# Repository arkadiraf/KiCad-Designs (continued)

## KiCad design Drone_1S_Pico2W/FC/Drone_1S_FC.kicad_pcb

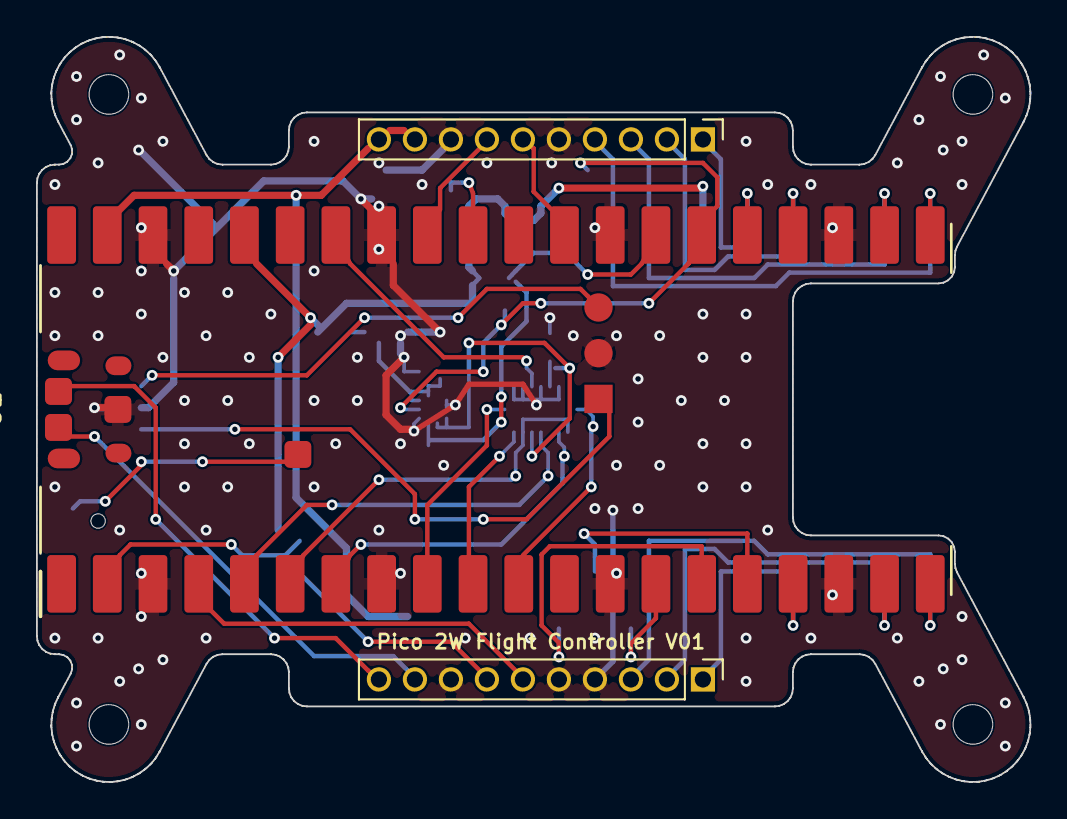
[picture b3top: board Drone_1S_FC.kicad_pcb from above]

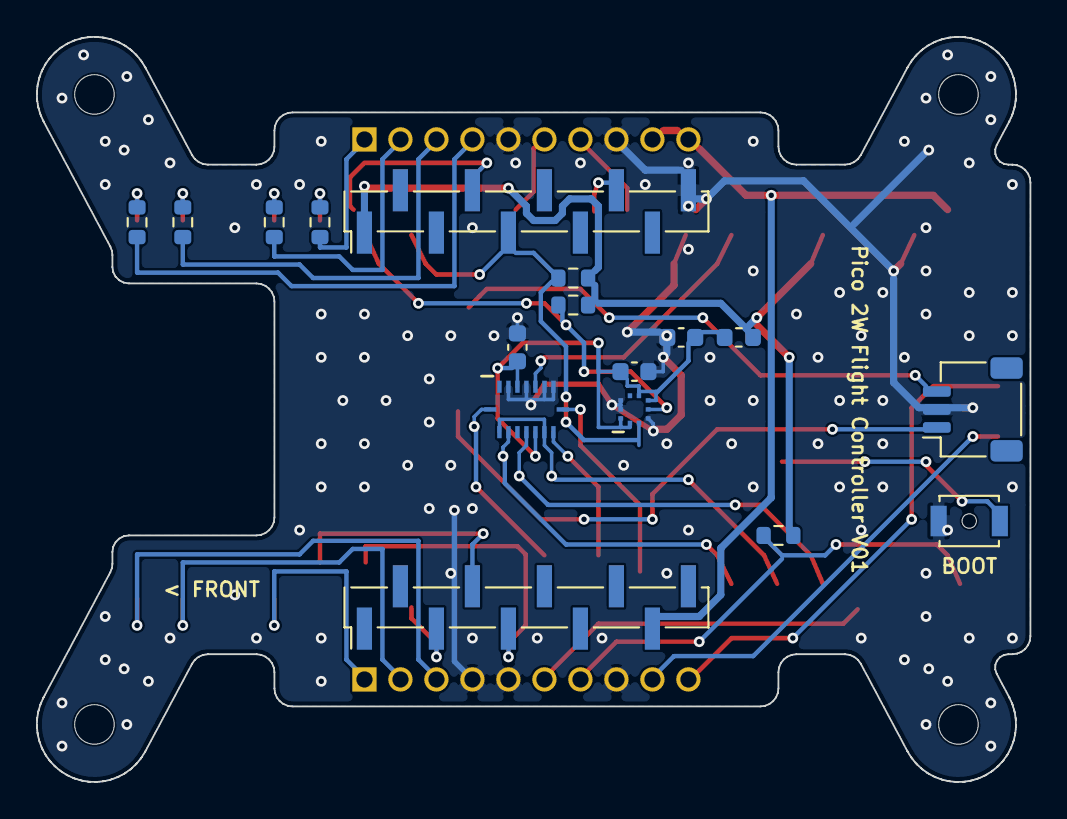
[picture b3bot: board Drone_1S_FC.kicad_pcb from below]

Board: 2 copper layers, 55.2 x 41.4 mm, 24 parts (17 on the bottom side), 37 nets.

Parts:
C1, C2: 100n; C_0603_1608Metric
C3: 4.7u; C_0603_1608Metric
H1, H2, H3, H4: M2x20 bolt + 7 mm spacer to frame; MountingHole_2.2mm_M2
J1, J2: Wurth 62001011121 header 1x10 2.00mm male (to fra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; PinHeader_1x10_P2.00mm_Vertical
J9: SWD (DNP): SWCLK, GND, SWDIO; JST_SH_SM03B-SRSS-TB_1x03-1MP_P1.00mm_Horizontal
L1: 1uH; L_0603_1608Metric
P1: Flow deck left (P1), male 1x10 2.00mm SMD; PinHeader_1x10_P2.00mm_Vertical_SMD_Pin1Left
P2: Flow deck right (P2), male 1x10 2.00mm SMD; PinHeader_1x10_P2.00mm_Vertical_SMD_Pin1Left
R1, R2: 4.7k; R_0603_1608Metric
R3, R4, R5, R6: 100; R_0603_1608Metric
R7: 47k; R_0603_1608Metric
SW1: BOOTSEL B3U-1000PM-B (Pico TP6 to GND); SW_SPST_B3U-1000P-B
U1: RPi_Pico_2_W; RPi_Pico_2_W_SMD_Castellated
U2: BMI088; Bosch_LGA-16_3x4.5mm_P0.5mm
U3: BMP390; Bosch_LGA-10_2x2mm_P0.5mm

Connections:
3V3: L1.1, P1.1, R1.1, R2.1, R7.1, U1.36
3V3_SENS: C1.1, C2.1, C3.1, L1.2, U2.3, U2.11, U3.1, U3.5, U3.6, U3.10
BOOST_EN: J1.6, U1.29
BOOTSEL: SW1.1, U1.TP6
CHG_PG: J1.7, U1.32
DSHOT1: J1.1, R3.2
DSHOT1_MCU: R3.1, U1.25
DSHOT2: J1.2, R4.2
DSHOT2_MCU: R4.1, U1.24
DSHOT3: J1.3, R5.2
DSHOT3_MCU: R5.1, U1.22
DSHOT4: J1.4, R6.2
DSHOT4_MCU: R6.1, U1.21
FLOW_CS: P1.8, U1.31
GND: C1.2, C2.2, C3.2, J1.5, J1.8, J2.4, J2.5, J2.8, J9.2, P1.10, SW1.2, U1.3, U1.8, U1.13, U1.18, U1.23, U1.28, U1.33, U1.38, U1.SWD_GND, U1.TP1, U2.2, U2.4, U2.6, U2.7, U3.3, U3.8, U3.9
I2C_SCL: P1.5, R2.2, U1.27, U3.2
I2C_SDA: P1.4, R1.2, U1.26, U3.4
IMU_CS_ACC: U1.7, U2.14
IMU_CS_GYR: U1.34, U2.5
IMU_INT_ACC: U1.11, U2.16
IMU_INT_GYR: U1.5, U2.12
MOTOR_PG: J2.7, R7.2, U1.2
ON1: J2.1, U1.17
ON2: J2.2, U1.19
ON3: J2.3, U1.20
ON4: J2.6, U1.4
SPI0_MISO: U1.6, U2.10, U2.15
SPI0_MOSI: U1.10, U2.9
SPI0_SCK: U1.9, U2.8
SPI1_MISO: P2.4, U1.16
SPI1_MOSI: P2.5, U1.15
SPI1_SCK: P2.3, U1.14
SWCLK: J9.1, U1.SWCLK
SWDIO: J9.3, U1.SWDIO
USB_DM: J2.10, U1.TP2
USB_DP: J2.9, U1.TP3
VSYS: J1.9, J1.10, P2.9, U1.39

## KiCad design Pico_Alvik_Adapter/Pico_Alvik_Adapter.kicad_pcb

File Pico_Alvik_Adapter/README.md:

# Pico Alvik Adapter

Adapter board that lets a **Raspberry Pi Pico W** replace the **Arduino Nano ESP32**
as the main controller of the **Arduino Alvik** robot (AKX00066).

* The Pico W is soldered **flat on the top side by its castellated edge pads**,
  with no pin headers between the boards.
* The bottom side carries two **1x15 2.54 mm SMD male headers in the Arduino Nano
  footprint**. They plug into the Alvik's Nano socket in place of the Nano ESP32.
* Every Nano pin the Alvik uses (UART, BOOT0, NRST, NANO_CHK, ROBOT_CHK, I2C,
  VIN, 3V3, GND) goes to a matching Pico pin: UART1 for the STM32 link and I2C1
  for the I2C bus. Seven spare Nano pins are wired as well.
* The micro-USB connector of the Pico sits at the same end as the Nano's USB-C,
  so it stays reachable through the Alvik's rear opening.

Designed in KiCad (files saved in KiCad 7 format; they open in KiCad 7, 8 and 9).

Individual renders are in `fabrication/docs/render_*.png`.

| | |
|---|---|
| Board size | 24.0 x 51.0 mm, 2 layers, 1.6 mm FR4 |
| Pico W | 21 x 51 mm module, top side, castellated SMD |
| Nano headers | 2x TE Connectivity 6-146132-3 (1x15 2.54 mm SMD male), bottom side, rows 15.24 mm apart |
| Antenna | 14 x 9 mm board notch under the Pico W antenna (datasheet keep-out) |

## Project layout

```
Pico_Alvik_Adapter.kicad_pro / .kicad_sch / .kicad_pcb   KiCad project
PicoAlvik.kicad_sym, PicoAlvik.pretty/                   project-local symbols & footprints
sym-lib-table, fp-lib-table                              library tables (use ${KIPRJMOD})
tools/                                                   generator scripts (design.py is the single source of truth)
firmware/                                                Alvik MicroPython library port kit for the Pico W
fabrication/                                             OSH Park gerbers (RS-274X) + drill, top/bottom stencils, BOM, positions, PDFs, renders
Materials/                                               datasheets / pinouts / schematics used for the design
```

## Pin mapping

Nano header pin numbers use the classic Nano numbering (1 = D1/TX ... 30 = VIN).

**Pins used by the Alvik** (from Arduino's `arduino-alvik-mpy` library, `pinout_definitions.py` and `uart.py`, plus the
Alvik datasheet block diagram; copies in `Materials/extracted/`):

| Nano pin | J1 | Pico GPIO | U1 pin | Alvik function | Pico peripheral |
|---|---|---|---|---|---|
| D1/TX1 | 1 | GP20 | 26 | UART TX -> STM32 RX (460800 baud) | UART1 TX |
| D0/RX0 | 2 | GP21 | 27 | UART RX <- STM32 TX | UART1 RX |
| D2 | 5 | GP22 | 29 | STM32 BOOT0 | |
| D3 | 6 | GP26 | 31 | STM32 NRST | |
| D4 | 7 | GP27 | 32 | NANO_CHK (EXT_CHK) | |
| A4/SDA | 23 | GP6 | 9 | I2C SDA (Qwiic / Grove, BMS, IMU...) | I2C1 SDA |
| A5/SCL | 24 | GP7 | 10 | I2C SCL | I2C1 SCL |
| A6 | 25 | GP8 | 11 | ROBOT_CHK (input) | |
| 3V3 | 17 | 3V3(OUT) | 36 | +3V3_EXT supply of the Alvik | via JP2 (bridged) |
| VBUS/VUSB | 27 | VBUS | 40 | Alvik power / charge input (USB 5V) | direct |
| VIN | 30 | VSYS | 39 | Alvik power output to the controller | D1 Schottky (opt. 0 Ω) |
| GND | 4, 29 | GND | 3,8,13,18,23,28,33,38 | | |
| RST | 3 | RUN | 30 | (not used by the Alvik) | via JP3 (open) |

**Spare Nano pins** (the Alvik leaves these unconnected). The ones that route cleanly are wired anyway:

| Nano pin | J1 | Pico GPIO | U1 pin | Note |
|---|---|---|---|---|
| D5 | 8 | GP28 | 34 | ADC2 |
| D13 | 16 | GP1 | 2 | |
| A0 | 19 | GP2 | 4 | |
| A1 | 20 | GP3 | 5 | |
| A2 | 21 | GP4 | 6 | |
| A3 | 22 | GP5 | 7 | |
| A7 | 26 | GP9 | 12 | |

Not connected: Nano D6–D12, B0, B1. Pico GP0, GP10–GP19,
ADC_VREF and 3V3_EN.

Each group is assigned in the same order on both sides, so its tracks never cross. The Nano-side
order is kept on the Pico's right edge (TX/RX/D2–D4) and left edge (A4–A6).

## Power design

How the Alvik uses the controller's power pins:

* **VBUS/VUSB (Nano pin 27):** the Alvik's power / battery-charge **input**. On a Nano this pin is raw
  USB 5V; the Nano schematic shows the USB-C VBUS pins tied straight to the `VUSB` header pin.
* **VIN (Nano pin 30):** the Alvik's power **output** to the controller. On a Nano, VIN is the input of
  its MP2322 regulator.

The adapter:

| Situation | Path |
|---|---|
| USB plugged into the Pico | Pico VBUS -> **Nano VUSB pin, direct** -> Alvik (powers the robot / charges the 18650) |
| | Pico VBUS -> Pico on-board Schottky -> VSYS (powers the Pico) |
| USB unplugged | Alvik VIN output -> **D1** -> VSYS (Alvik powers the Pico) |
| Both present | VSYS is diode-OR'ed (D1 / Pico diode); the higher source supplies the Pico |

* **D1: Nexperia PMEG6020ER,115** (2 A / 60 V Schottky, SOD-123W, anode = VIN; Digi-Key 1727-5217-1-ND;
  datasheet in `Materials/`, KiCad pads match its reflow land pattern 1.2 x 1.2 mm at 2.8 mm pitch). It stops the USB-derived
  VSYS (about 4.7 V) from back-feeding the Alvik's VIN output, in case the Alvik has no diode of its own
  there. Blocking that direction costs nothing, because the Alvik takes its power from VUSB, not VIN.
* **Option: 1206 0 Ω on the D1 pads.** This removes the ~0.35 V drop and matches a Nano exactly, where
  VIN is the regulator input with no diode and USB reaches VIN through the Nano's own PMEG6020. Only fit
  it if you know the Alvik's VIN output tolerates that.
* Charge current flows from the Pico's micro-USB straight to the VUSB pin. It does not pass through the
  Pico's 1 A on-board diode, or through D1.
* **VSYS range is 1.8–5.5 V.** The Alvik VIN output minus the D1 drop is inside that range.
* **JP2 (bridged):** Pico 3V3(OUT) -> Nano 3V3 pin. On the Nano, 3V3 is the output of its regulator,
  and on the Alvik it feeds `+3V3_EXT` (the I2C switch supply). Keep the 3V3 load under 300 mA. If you
  ever measure about 3.3 V on the Alvik's 3V3 socket pin with no controller fitted, cut JP2.
* **JP3 (open):** optional, Nano RST -> Pico RUN.
* C1: 10 µF on VSYS.

**Bring-up check:** with the adapter removed and the Alvik switched on, measure the Alvik's Nano socket.
VIN (pin 30) should be ≤ 5.5 V. VUSB (pin 27) and 3V3 (pin 17) should be about 0 V.

## Manufacturing

`fabrication/README.md` covers ordering and assembly. In short:

* **PCB:** `fabrication/Pico_Alvik_Adapter_OSHPark.zip`, RS-274X Gerbers with Protel names
  (`.GTL/.GBL/.GTS/.GBS/.GTO/.GBO/.GKO`) plus Excellon `.XLN`. Designed to OSH Park's rules: copper
  ≥ 0.4 mm from the board edge, drills ≥ 0.3 mm, silkscreen strokes ≥ 0.15 mm.
* **Stencils:** `fabrication/Pico_Alvik_Adapter_stencil_top.zip` (Pico W pads, over-pasted to
  3.8 × 2.2 mm per the Pico W datasheet) and `..._stencil_bottom.zip` (headers, C1, D1). Each comes
  with the board outline for alignment.

## Mechanical notes

* The SMD headers keep the top copper flat under the Pico W, because Nano rows (15.24 mm) and
  Pico rows (17.78 mm) overlap and through-hole joints would short against the Pico's pins.
* Copper is kept out from under the Pico W test points TP1–TP6 and the SWD pads (datasheet §2.2).
  Vias are tented.
* The board is 24 mm wide (Nano: 18 mm). Check the clearance inside the Alvik's
  top cover before ordering.
* Bottom-side parts (C1, D1, jumpers) sit between the header rows and are at most about 1.2 mm high.
* **Headers: TE Connectivity 6-146132-3** (Digi-Key A124546-ND), 1x15, 2.54 mm, 0.63 mm square post,
  5.84 mm mating length, matte tin. The J1 pads follow TE's recommended layout (drawing C-146132 rev N2,
  `Materials/TE_6-146132_drawing_C-146132_N2.pdf`): 1.27 x 3.56 mm, staggered +-1.335 mm. The legs
  alternate sides, so each header fits the staggered pads only one way round.
* Stack height: the TE body stands about 4 mm off the PCB, versus 2.5 mm for a through-hole Nano header,
  so the adapter sits roughly 1.5 mm higher in the Alvik than a Nano does. Check the top-cover clearance
  (Pico W plus this extra height) before ordering in quantity.

## Firmware

`firmware/` holds a port kit for Arduino's Alvik MicroPython library: updated
`pinout_definitions.py` and `uart.py`, plus `port_alvik_to_pico.py`, which patches a stock
library copy. The patches cover UART1 on GP20/GP21, I2C1 on GP6/GP7, the STM32 firmware updater's
pins, and the LED. See `firmware/README.md` for usage and limitations (one extra thread on the
RP2040). `tools/check_firmware.py` verifies the firmware pin map against `design.py`.

## Regenerating the design

The schematic, libraries and PCB are produced by the scripts in `tools/`
from `tools/design.py`:

```sh
cd tools
python3 gen_libs.py                 # PicoAlvik.kicad_sym + PicoAlvik.pretty
python3 gen_schematic.py            # Pico_Alvik_Adapter.kicad_sch
kicad-cli sch export netlist -o ../build/net.net ../Pico_Alvik_Adapter.kicad_sch
python3 check_netlist.py ../build/net.net     # schematic == design.py ?
/usr/bin/python3 gen_pcb.py place   # placement, outline, keep-outs (+ .dsn for Freerouting)
/usr/bin/python3 gen_pcb.py geom    # geometry for the router
python3 router.py                   # 2-layer A* grid router -> build/routes.json
/usr/bin/python3 gen_pcb.py finish  # import routes, GND pours, zone fill, DRC report
bash export_fab.sh                  # gerbers, drill, BOM, PDFs
python3 render_board.py             # renders in fabrication/docs/ (flat + angled)
```

Status of the checked-in board (v1.7): all nets routed, **KiCad DRC: 0 violations, 0 unconnected
pads, 0 footprint errors** (`build/` is regenerated and not committed).

The v1.7 files were generated with **KiCad 10** on Windows (the `.kicad_pcb` is now KiCad 10 format; the
schematic keeps the KiCad 7 format). With KiCad 9+ run the PCB scripts with KiCad's own python
(`"C:\Program Files\KiCad\10.0\bin\python.exe" gen_pcb.py ...`). `gen_pcb.py finish` skips
`WriteDRCReport` (it needs the GUI) — run `kicad-cli pcb drc --severity-all -o build/drc_report.txt
Pico_Alvik_Adapter.kicad_pcb` instead. KiCad 9+ `kicad-cli sch erc` reports two `lib_symbol_mismatch`
warnings for the solder jumpers (embedded KiCad 7 symbol copies); they are cosmetic. KiCad 7's command line has no ERC, so the
schematic is verified with `check_netlist.py`, which compares KiCad's exported netlist to `design.py`.
Running ERC once in the KiCad GUI is still worthwhile.

`gen_pcb.py place` also writes `build/Pico_Alvik_Adapter.dsn`. If you prefer Freerouting,
route that file, save the `.ses` as `build/Pico_Alvik_Adapter.ses`, delete
`build/routes.json`, and run `gen_pcb.py finish`.

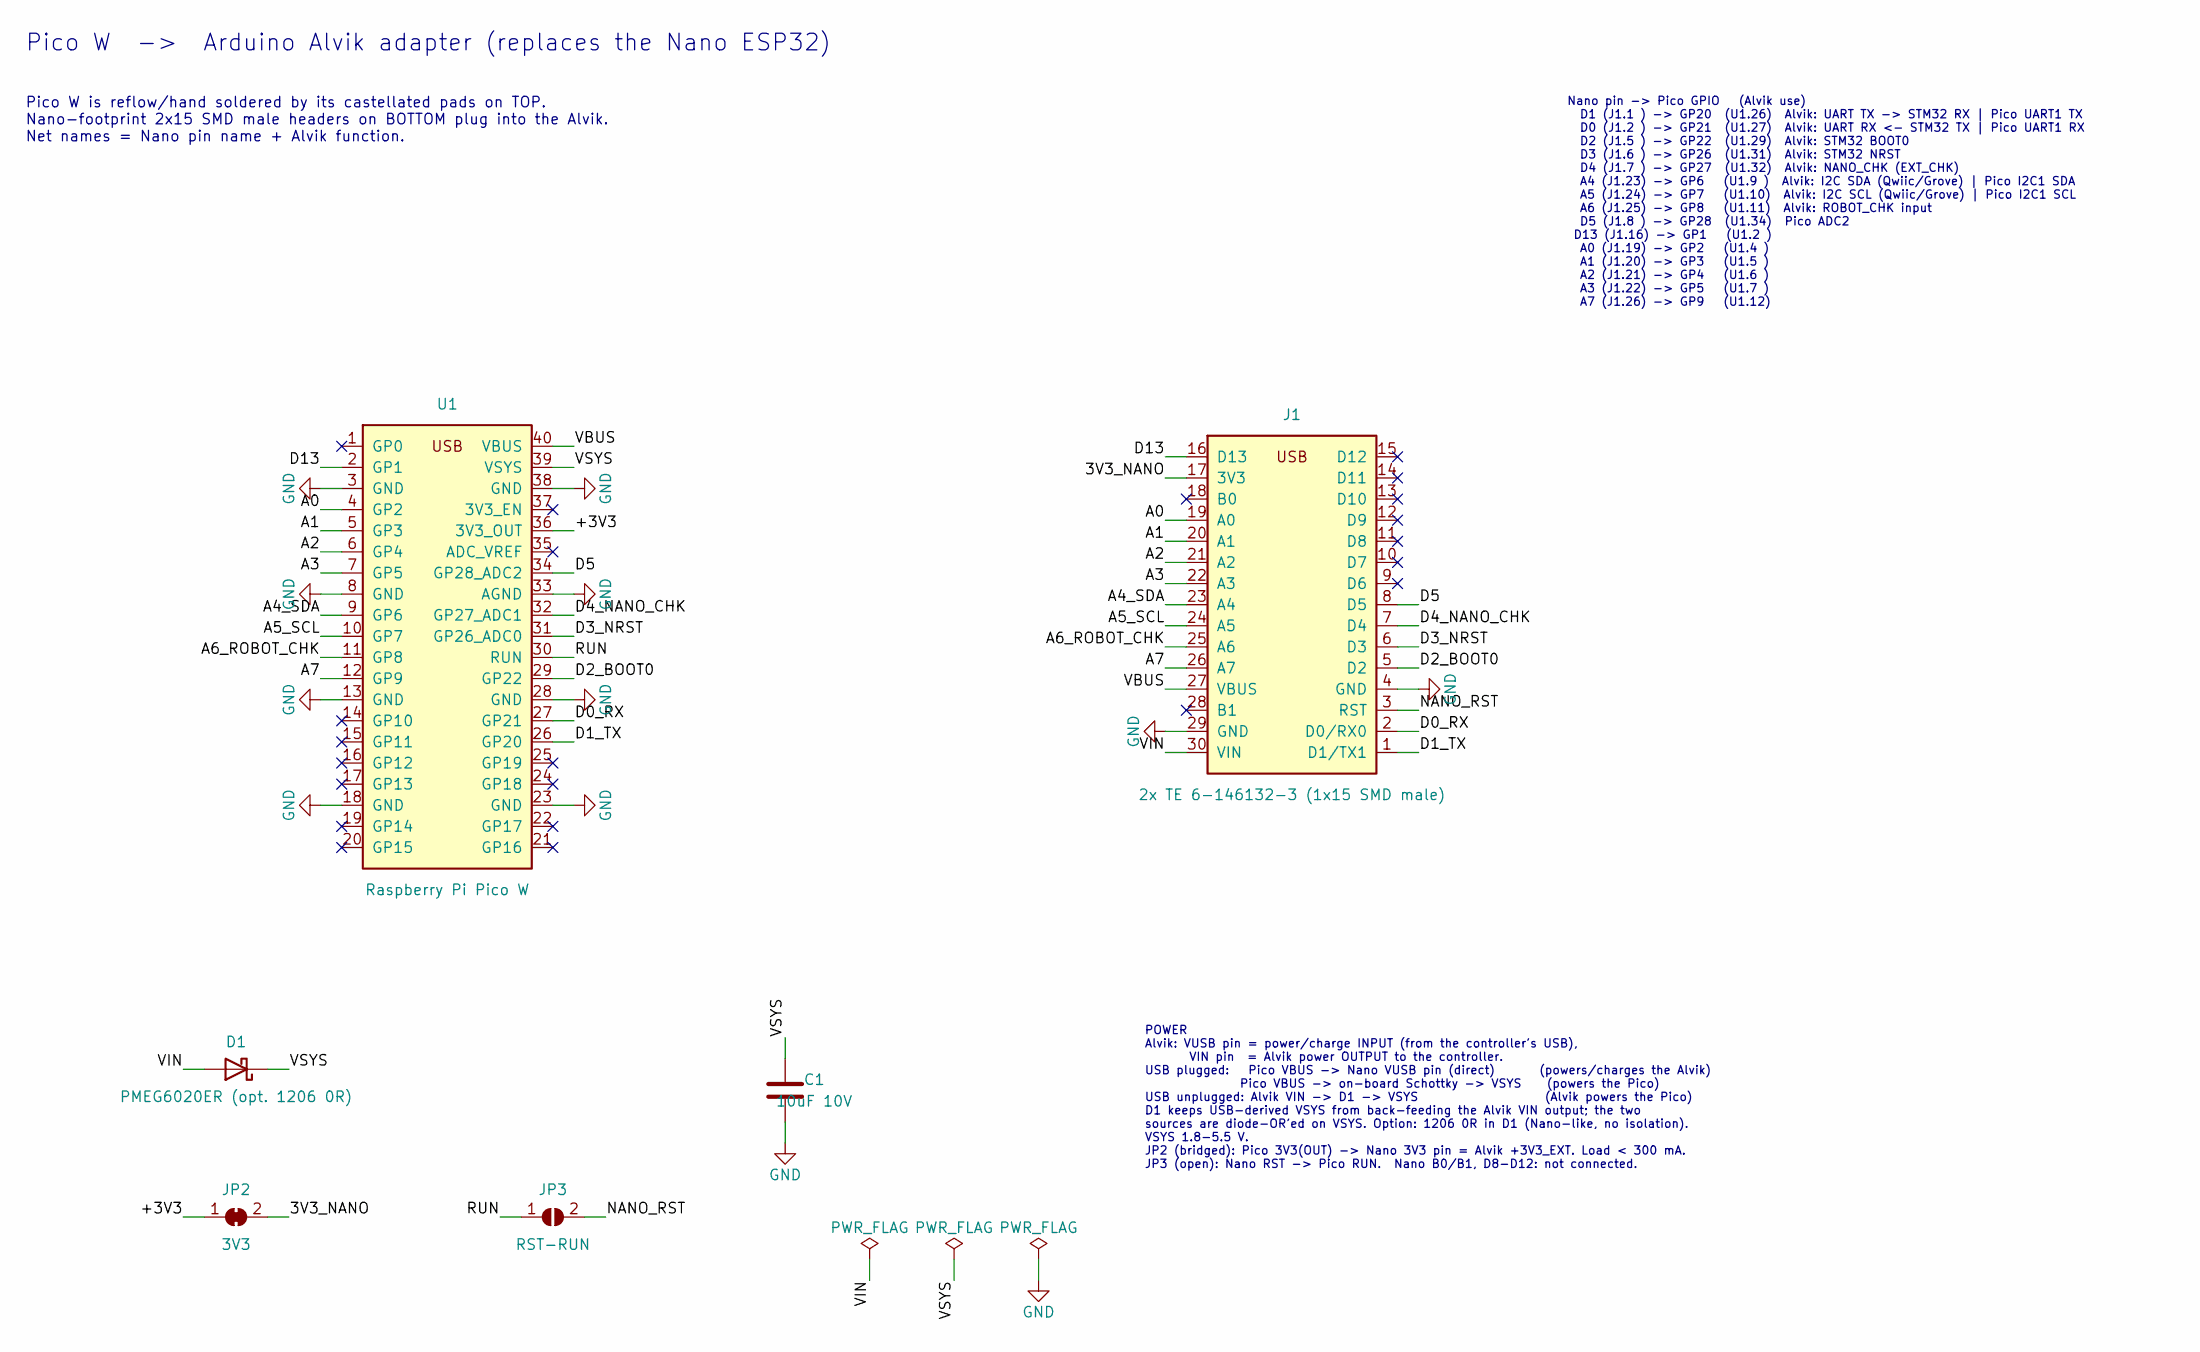
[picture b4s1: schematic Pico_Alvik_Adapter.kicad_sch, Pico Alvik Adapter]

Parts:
C1: 10uF 10V; C_0805_2012Metric
D1: PMEG6020ER (opt. 1206 0R); Nexperia_CFP3_SOD-123W
J1: 2x TE 6-146132-3 (1x15 SMD male); Arduino_Nano_SMD_Headers_Bottom
JP2: 3V3; SolderJumper-2_P1.3mm_Bridged_RoundedPad1.0x1.5mm
JP3: RST-RUN; SolderJumper-2_P1.3mm_Open_RoundedPad1.0x1.5mm
U1: Raspberry Pi Pico W; RPi_Pico_W_SMD_Castellated

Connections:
3V3_NANO: J1.17 (3V3), JP2.2 (B)
+3V3: JP2.1 (A), U1.36 (3V3_OUT)
A0: J1.19 (A0), U1.4 (GP2)
A1: J1.20 (A1), U1.5 (GP3)
A2: J1.21 (A2), U1.6 (GP4)
A3: J1.22 (A3), U1.7 (GP5)
A4_SDA: J1.23 (A4), U1.9 (GP6)
A5_SCL: J1.24 (A5), U1.10 (GP7)
A6_ROBOT_CHK: J1.25 (A6), U1.11 (GP8)
A7: J1.26 (A7), U1.12 (GP9)
D0_RX: J1.2 (D0/RX0), U1.27 (GP21)
D1_TX: J1.1 (D1/TX1), U1.26 (GP20)
D2_BOOT0: J1.5 (D2), U1.29 (GP22)
D3_NRST: J1.6 (D3), U1.31 (GP26_ADC0)
D4_NANO_CHK: J1.7 (D4), U1.32 (GP27_ADC1)
D5: J1.8 (D5), U1.34 (GP28_ADC2)
D13: J1.16 (D13), U1.2 (GP1)
GND: C1.2, J1.4 (GND), J1.29 (GND), U1.3 (GND), U1.8 (GND), U1.13 (GND), U1.18 (GND), U1.23 (GND), U1.28 (GND), U1.33 (AGND), U1.38 (GND)
NANO_RST: J1.3 (RST), JP3.2 (B)
RUN: JP3.1 (A), U1.30 (RUN)
VBUS: J1.27 (VBUS), U1.40 (VBUS)
VIN: D1.2 (A), J1.30 (VIN)
VSYS: C1.1, D1.1 (K), U1.39 (VSYS)

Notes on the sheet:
Pico W -> Arduino Alvik adapter (replaces the Nano ESP32)
Pico W is reflow/hand soldered by its castellated pads on TOP. Nano-footprint 2x15 SMD male headers on BOTTOM plug into the Alvik. Net names = Nano pin name + Alvik function.
Nano pin -> Pico GPIO (Alvik use) D1 (J1.1 ) -> GP20 (U1.26) Alvik: UART TX -> STM32 RX | Pico UART1 TX D0 (J1.2 ) -> GP21 (U1.27) Alvik: UART RX <- STM32 TX | Pico UART1 RX D2 (J1.5 ) -> GP22 (U1.29) Alvik: STM32 BOOT0 D3 (J1.6 ) -> GP26 (U1.31) Alvik: STM32 NRST D4 (J1.7 ) -> GP27 (U1.32) Alvik: 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
POWER Alvik: VUSB pin = power/charge INPUT (from the controller's USB), VIN pin = Alvik power OUTPUT to the controller. USB plugged: Pico VBUS -> Nano VUSB pin (direct) (powers/charges the Alvik) Pico VBUS -> on-board Schottky -> VSYS (powers the Pico) USB unplugged: Alvik VIN -> D1 -> VSYS (Alvik 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

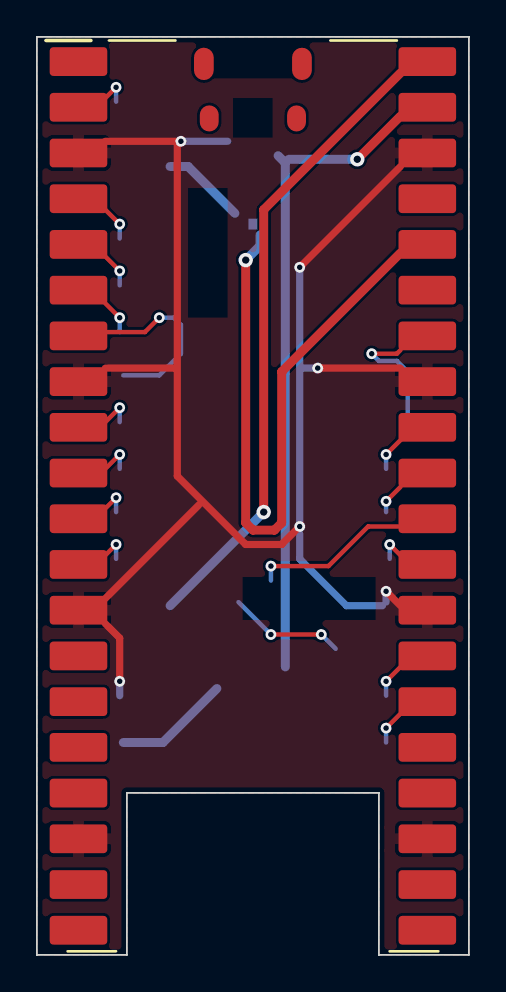
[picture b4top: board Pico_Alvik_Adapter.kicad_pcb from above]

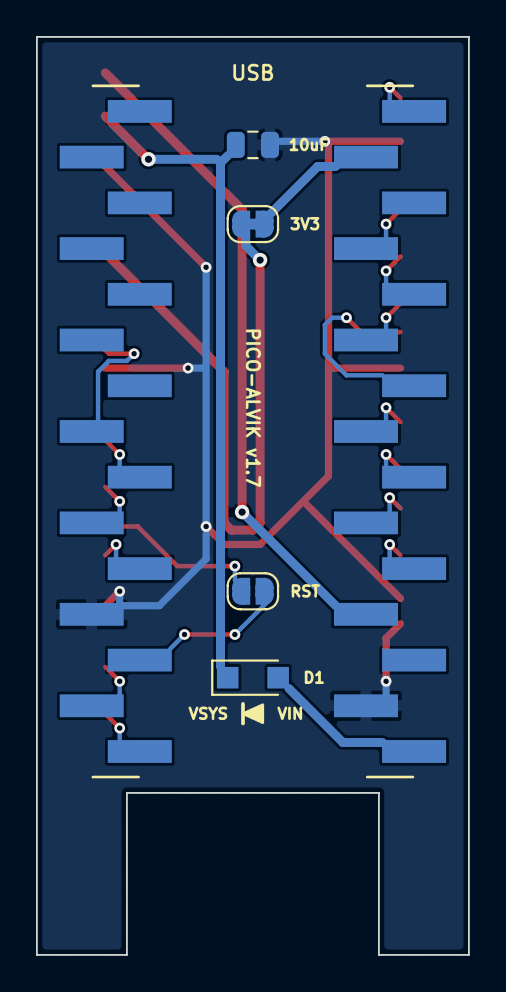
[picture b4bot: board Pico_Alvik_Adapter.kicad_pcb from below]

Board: 2 copper layers, 24.0 x 51.0 mm, 6 parts (5 on the bottom side), 23 nets.

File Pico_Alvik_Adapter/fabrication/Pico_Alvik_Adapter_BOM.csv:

References,Qty,Value,Footprint,Populate,Notes
C1,1,10uF 10V,Capacitor_SMD:C_0805_2012Metric,yes,MLCC 10uF 10V X5R 0805
D1,1,PMEG6020ER (opt. 1206 0R),Diode_SMD:Nexperia_CFP3_SOD-123W,yes,"Nexperia PMEG6020ER Schottky 2A/60V SOD-123W, Digi-Key 1727-5217-1-ND. Anode = Nano VIN (Alvik output), cathode = Pico VSYS. Optional: 1206 0R if the Alvik VIN output tolerates back-feed"
J1,1,2x TE 6-146132-3 (1x15 SMD male),PicoAlvik:Arduino_Nano_SMD_Headers_Bottom,yes,"2x TE Connectivity 6-146132-3 (1x15 2.54mm SMD male, matte tin; Digi-Key A124546-ND)"
JP2,1,3V3,Jumper:SolderJumper-2_P1.3mm_Bridged_RoundedPad1.0x1.5mm,yes,"solder jumper, bridged by default (cut to isolate)"
JP3,1,RST-RUN,Jumper:SolderJumper-2_P1.3mm_Open_RoundedPad1.0x1.5mm,yes,"solder jumper, open by default"
U1,1,Raspberry Pi Pico W,PicoAlvik:RPi_Pico_W_SMD_Castellated,yes,"Raspberry Pi Pico W (SC0918), solder by castellated pads, no headers"

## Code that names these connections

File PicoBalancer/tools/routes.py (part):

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#   * D+ : A6 -> B6 diagonal in the row gap (0.15 mm, 0.22 mm clearance to A7 / B7).
#   * D- : A7 -> via above the rows -> bottom -> via below the rows <- B7 (the reversible pairs cross).
#   * CC1 (A5, enclosed by the VBUS loop) -> via -> bottom -> R13; CC2 (B5) -> R14 on top.
#   * D+ / D- run on the bottom down the channel to vias beside U6 pins 3 / 4 (BC1.2 detection only, low speed).
# ===================================================================================================================
for x in (-2.75, 2.75):                                          # GND A1-B12, A12-B1
    T("GND", 0.3, (x, -93.86), (x, -92.14))
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# 1b. Charger U6 BQ25606 (rotated 180: bottom row y -45.04 = SW SW BTST REGN PMID VBUS, x -1.25 .. 1.25; left column
#     x -1.96 = GND GND SYS SYS BAT BAT (y -45.75 .. -48.25); right column x 1.96 = VAC NC D+ D- STAT GND; top row
#     y -48.96 = VSET TS ICHG GND ILIM PG; exposed pad 2.7 mm = GND)
#   * SW pins -> L1 pad 1 straight down (0.5 -> 0.8 mm); BTST cap C27 right under pin 21; REGN cap C26 below it;
#     PMID -> C21 / C22 (0.6 mm); VBUS / VAC joined round the corner -> C20 -> the lane.
#   * SYS: L1 pad 2 -> C23 / C24 -> pins 15 / 16 (1.0 mm); BAT: pins 13 / 14 -> C25 -> 1.2 mm trunk down the left side
#     of the channel (x -8) to the cells.
#   * Signals escape to vias (router continues): PG, ILIM, ICHG, TS up; STAT, D+, D- right. VSET stays unconnected:
#     no copper on pin 12 (4.208 V).
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#   * CELL+ 2.0 mm on BOTH layers (vias 0.8 / 0.4 along it), from the + pad down beside the holder at |x| 15 (>= 0.4 mm
#     from the 3.45 mm locating hole and the - pad) to the fuse pad 1; up to ~2.2 A per cell.
#   * fuse pad 2 -> FET drain pad (1.5 mm); FET sources joined by a bar -> one 1.2 mm BAT bus across the board
#     (y 6.4 left, 5.6 right: clear of each FET's gate pin), joined by the charger's BAT trunk (x -8).
#   * holder - pads: GND vias in front of each pad (+ the pours).
#   * gate / sense parts (Q3 Q4, R28-R33) by the router, except the short gate stubs at the FET pins.
# ===================================================================================================================
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
# ===================================================================================================================
# 5. Pico power path (right column): BAT -> SW1 leg (R34) / TPS22810 U7 VIN + C28; U7 VOUT (VSW) -> C29, D2 anode,
#    R24 (DNP bypass); D2 cathode (VSYS) -> Pico VSYS pin 39 on the BOTTOM (crosses BAT and the Pico's 3V3 / VBAT_SENSE
#    escapes without a conflict). UVLO divider, LEDs, VBAT sense and EN by the router (signal currents).
# ===================================================================================================================
T("BAT", 0.6, (6.5, 6.0), (6.5, 14.8), (7.1, 15.4), (12.9, 15.4), (13.5, 16.0), (13.5, 37.6), (18.6, 37.6),
  (18.9, 38.25), (18.9, 38.55))
T("BAT", 0.4, (13.5, 27.82), (15.2, 27.82))                                     # R34 (switch BAT leg)
T("BAT", 0.4, (15.5, 37.6), (15.5, 38.72))                                      # C28 pad 1
T("VSW", 0.4, (21.39, 38.55), (21.39, 39.5))                                    # U7 VOUT pins 5 / 6
T("VSW", 0.6, (21.39, 39.5), (22.6, 39.5), (22.6, 44.5), (21.65, 44.5))          # -> D2 anode
T("VSW", 0.4, (22.6, 40.28), (25.0, 40.28))                                     # C29
T("VSW", 0.4, (21.65, 44.5), (21.07, 47.0))                                     # R24 (rotated: VSW pad right)
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
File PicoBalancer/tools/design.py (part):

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}

# ---------------------------------------------------------------------------
# Pin map v2 (Pico W and Pico 2 W, user-approved 2026-11-27), matched to the placement: USB end up, so pins 1-20 run
# down the left side and 21-40 up the right side. GP23/24/25/29 belong to the CYW43439 on both modules.
PINMAP = {
    0: "SPARE", 1: "SPARE",                            # left, top: spare (UART0 debug header J6 dropped, user 2026-11-27)
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    18: "SPARE", 19: "USER_LED",                       # right: GP18 spare, D4 user LED
    20: "M2_IN1", 21: "M2_IN2",                        # right motor, PWM slice 2 A/B
    22: "IMU_WAKE",                                    # right
    26: "M1_ISENSE", 27: "M2_ISENSE", 28: "VBAT_SENSE",   # right, the only ADC pins
}

# ---------------------------------------------------------------------------
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    # USB-C at the top edge, CC resistors and VBUS cap beside it (channel x +-8.9 between the holder courtyards)
    "J5": (0.0, -93.0, 0), "C20": (4.3, -44.6, 270), "R13": (-3.0, -89.3, 270), "R14": (1.8, -89.3, 270),
    # charger below the cover pillar (y > -56), stage-3 routing layout: U6 rotated 180 so its SW / BTST / REGN / PMID /
    # VBUS row faces down; L1 (rotated) SW pad right under the SW pins, then the BTST, REGN and PMID caps in pin order,
    # the VBUS cap at the VBUS / VAC corner, SYS caps on the left, the BAT cap at the top-left corner
    "R15": (-6.0, -29.0, 90), "R16": (-3.0, -29.0, 90), "R17": (0.0, -29.0, 90), "R18": (3.0, -29.0, 90),
    "R19": (6.0, -29.0, 90),
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
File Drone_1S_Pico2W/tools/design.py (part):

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#  - so the four motor-switch ON lines stay separate (staggered turn-on, a faulted ESC can
#    be switched off alone), and three GND.
# 2026-11-28 (user): the four TPS22997 PG outputs are tied together on the frame (open drain, wired-AND) into one
# MOTOR_PG line (47k pull-up R7 on the FC): it frees the GPIOs the Pico 2 W lacks (27 needed, 26 free). Firmware finds
# a faulted ESC by switching the ON lines one at a time. Pin k of J1 (+y) / J2 (-y), k = 1 at the front (x = 9).
# The order follows the Pico pins they come from, so the FC side routes without crossings where it can.
B2B_J1 = ["DSHOT1", "DSHOT2", "DSHOT3", "DSHOT4", "GND", "BOOST_EN", "CHG_PG", "GND", "VSYS", "VSYS"]
B2B_J2 = ["ON1", "ON2", "ON3", "GND", "GND", "ON4", "MOTOR_PG", "GND", "USB_DP", "USB_DM"]   # USB on the end pins: straight in from the rear
B2B_SIGNALS = B2B_J1 + B2B_J2
assert len(B2B_J1) == len(B2B_J2) == B2B["pins"]

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FRAME_CONN = [
    # J7 Pi USB: the Pi Zero 2 W is the USB host for the Pico (programming with picotool,
    # USB serial link, boot/shutdown handshake). No VBUS: the Pico runs from VSYS, and VBUS
    # would back-feed VSYS through the Pico's Schottky. 4 pins (GND, D-, D+, GND) so it cannot be
    # confused with the 3-pin SWD connector J9.
    # 2026-11-28 (user): VERTICAL (top-entry BM04B) so the lead goes straight up to the Pi, beside the Pi's USB edge:
    # the Pi Zero 2 W (scad: centred, SD end at the rear) has its micro-USB ports on its -y edge, USB data (OTG) at
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    # -> 2.54 mm pitch, 1.0 mm drill. Stands next to the cell, bead bent onto it and taped.
    ("TH1", "10k NTC 103AT-2", "Device:Thermistor_NTC", "Connector_PinHeader_2.54mm:PinHeader_1x02_P2.54mm_Vertical",
     "cell temperature for the BQ25606 TS pin (0-60 C window with R5/R6)"),
    # Datasheet pin table: 1 uF on VBUS close to the IC, 10 uF on PMID; 10.2.2.2: ~22 uF input for 3 A charging
    # -> 2 x 10 uF on PMID (the input capacitor of the buck, placed first in the layout order).
    ("C1", "1uF 25V", "Device:C", _C, "VBUS, close to pin 24 (VBUS up to 13.5 V)"),
    ("C2 C23", "10uF 25V", "Device:C", _C08, "PMID, buck input (~22 uF total for 3 A)"),
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    ("R7", "2.2k", "Device:R", _R, "STAT LED series resistor (STAT sinks 6 mA max)"),
    # --- logic rail: TPS22810 + slide switch ---
    # UVLO (user 2026-11-28): the INTERNAL lockout, 2.54 V on / 2.41 V off, so the drone keeps flying long enough
    # to land; firmware warns and lands well above it (VSYS on GPIO29). R8-R10 stay a DNP option.
    ("U2", "TPS22810DBV", "KD_Power:TPS22810DBV", "Package_TO_SOT_SMD:SOT-23-6", "Pico VSYS switch, internal 2.54 / 2.41 V UVLO"),
    # Nidec Components CUS-12TB (Digi-Key 563-1102-1-ND; user 2026-11-28 - the APEM MA12R/TR is obsolete). Nidec CUS
    # catalog (2024-03) recommended pad layout = KiCad SW_SPDT_PCM12: terminals 0.7 x 1.5 mm at -2.25 / +0.75 / +2.25 mm,
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     "external 3.22 / 2.65 V UVLO divider (E24 150k) - NOT fitted: the internal 2.54 / 2.41 V lockout is the choice (user 2026-11-28)"),
    # Back-feed Schottky (user 2026-11-28, as PicoBalancer D2): TPS22810 VOUT -> D2 -> VSYS (to the FC). With the Pico's
    # own micro-USB plugged in on the bench, VBUS -> the Pico's Schottky -> VSYS would otherwise back-feed the
    # TPS22810 output. Costs ~0.3 V at the Pico (its buck-boost runs down to 1.8 V); GPIO29 reads VSYS after D2.
    ("D2", "Schottky 20V 1A (MBR120VLSFT1G)", "Device:D_Schottky", "Diode_SMD:D_SOD-123F",
     "TPS22810 VOUT -> VSYS, blocks back-feed from the Pico's own USB"),
    # --- motor switches: 4 x TPS22998 (2026-11-28, user: TPS22997RYZR out of stock) ---
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    # = 1.23 ms at 3.3 V, open = 0.15 ms. R15-R18 0R to GND (the old CT-capacitor pads): fitted = slow soft start.
    ("R15 R16 R17 R18", "0R", "Device:R", _R, "CT strap to GND: slowest rise ~2.5 ms (DNP = fast)"),
    ("R11 R12 R13 R14", "100k", "Device:R", _R, "ON pull-downs: Pico off = motors off"),
    # PG: the TPS22998 has none, so the frame leaves J6 pin 7 (MOTOR_PG) unconnected; the FC's 47k pull-up R7 holds it
    # high (reads "good" always) - no FC change. A faulted ESC is found by switching the ON lines one at a time.
    # --- optional 5.1 V boost for the Pi Zero ---
    ("U7", "TPS61235P", "KD_Power:TPS61235P", "KD_Power:Texas_RWL_VQFN-HR-9_2.5x2.5mm_P0.5mm", "5.1 V boost, true disconnect"),
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
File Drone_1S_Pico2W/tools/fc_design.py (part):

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    14: "ON2",              # J2.2
    15: "ON3",              # J2.3
    16: "DSHOT4_MCU",       # -> R6 100R -> J1.4   (order reversed so the four paths nest without crossing;
    17: "DSHOT3_MCU",       # -> R5 -> J1.3          firmware maps the PIO pins to motors)
    18: "DSHOT2_MCU",       # -> R4 -> J1.2
    19: "DSHOT1_MCU",       # -> R3 -> J1.1
    20: "I2C_SDA",          # BMP390 + Flow deck left 4 (VL53L1X), 4.7k pull-up R1
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    22: "BOOST_EN",         # J1.6 (100k pull-down on the frame)
    26: "FLOW_CS",          # Flow deck left 8 = IO_3 (PMW3901 CS)
    27: "CHG_PG",           # J1.7 (BQ25606 PG, open drain, pulled up on the frame side)
    28: "IMU_CS_GYR",       # BMI088 CSB2 (its escape via is on the +y side, next to this pin row)
}
PICO_GP_PIN = {0: 1, 1: 2, 2: 4, 3: 5, 4: 6, 5: 7, 6: 9, 7: 10, 8: 11, 9: 12, 10: 14, 11: 15, 12: 16, 13: 17, 14: 19,
               15: 20, 16: 21, 17: 22, 18: 24, 19: 25, 20: 26, 21: 27, 22: 29, 26: 31, 27: 32, 28: 34}
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        ("Power flags: GND and VSYS enter on J1 (from the frame); 3V3_SENS is fed through L1", 500.38, 312.42, 1.27),
        ("MOTOR_PG: the frame ties the four TPS22997 PG outputs together (wired-AND); 47k pull-up R7 here." + chr(10) +
         "3V3_SENS: BMI088 + BMP390 supply through L1 / C3 against motor noise (Crazyflie Bolt 1.1)." + chr(10) +
         "VBUS (Pico pin 40) is unused: the Pico runs from VSYS; USB D+/D- go to the frame (Pi Zero host)." + chr(10) +
         "DNP: J9 (SWD).  Design doc: docs/Toothpick_Drone_Hardware_Design_1S_Pico2W.pdf", 20, 395, 1.5),
    ],
)
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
